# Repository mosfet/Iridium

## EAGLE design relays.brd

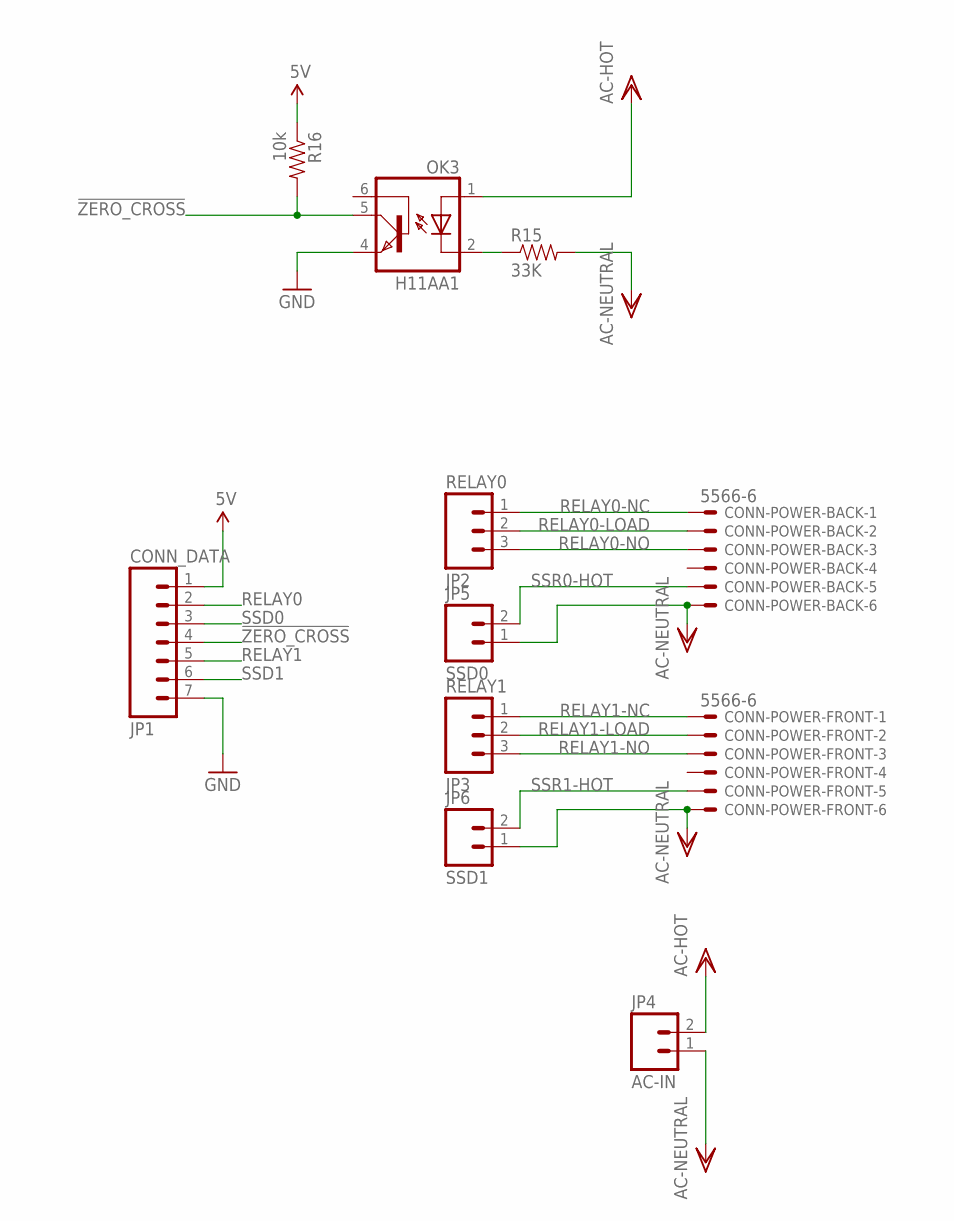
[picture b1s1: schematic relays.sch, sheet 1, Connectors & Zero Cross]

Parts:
CONN-POWER-BACK: 5566-6
CONN-POWER-FRONT: 5566-6
JP1: CONN_DATA; 1X07_LONGPADS
JP2: RELAY0; SCREWTERMINAL-5MM-3
JP3: RELAY1; SCREWTERMINAL-5MM-3
JP4: AC-IN; SCREWTERMINAL-5MM-2
JP5: SSD0; SCREWTERMINAL-5MM-2
JP6: SSD1; SCREWTERMINAL-5MM-2
OK3: H11AA1; DIL6-SMD
R15: 33K; 0603-RES
R16: 10k; 0603-RES

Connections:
5V: JP1.1, R16.1; also elsewhere on the board
!ZERO_CROSS: JP1.4, OK3.5 (COL), R16.2
AC-HOT: JP4.2, OK3.1 (A); also elsewhere on the board
AC-NEUTRAL: CONN-POWER-BACK.6, CONN-POWER-FRONT.6, JP4.1, JP5.1, JP6.1, R15.2
GND: JP1.7, OK3.4 (EMI); also elsewhere on the board
unnamed: OK3.2 (C), R15.1
RELAY0: JP1.2; also elsewhere on the board
RELAY0-LOAD: CONN-POWER-BACK.2, JP2.2; also elsewhere on the board
RELAY0-NC: CONN-POWER-BACK.1, JP2.1; also elsewhere on the board
RELAY0-NO: CONN-POWER-BACK.3, JP2.3; also elsewhere on the board
RELAY1: JP1.5; also elsewhere on the board
RELAY1-LOAD: CONN-POWER-FRONT.2, JP3.2; also elsewhere on the board
RELAY1-NC: CONN-POWER-FRONT.1, JP3.1; also elsewhere on the board
RELAY1-NO: CONN-POWER-FRONT.3, JP3.3; also elsewhere on the board
SSD0: JP1.3; also elsewhere on the board
SSD1: JP1.6; also elsewhere on the board
SSR0-HOT: CONN-POWER-BACK.5, JP5.2; also elsewhere on the board
SSR1-HOT: CONN-POWER-FRONT.5, JP6.2; also elsewhere on the board

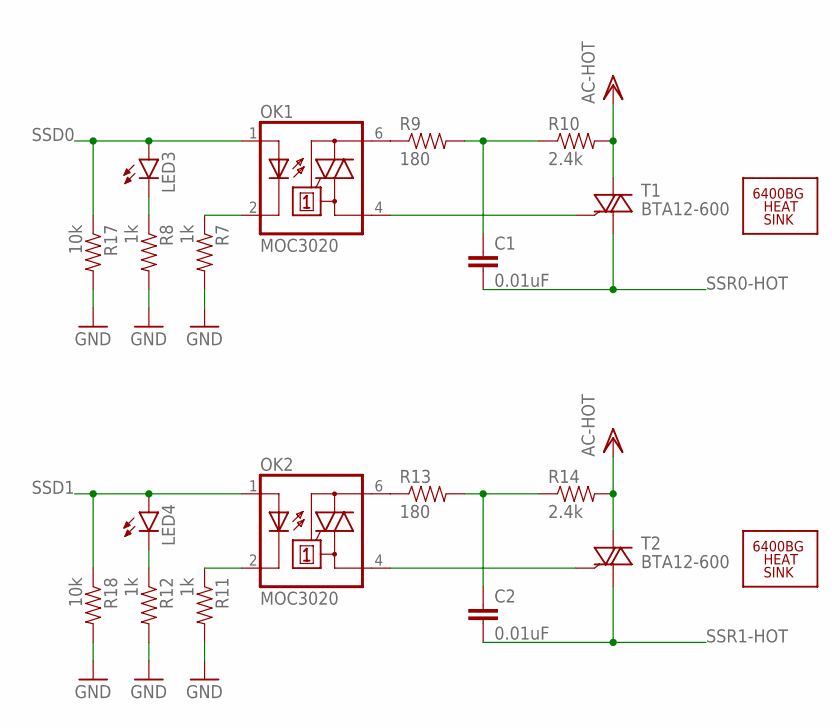
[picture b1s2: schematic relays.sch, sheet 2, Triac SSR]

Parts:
C1, C2: 0.01uF; 0603-CAP
LED3, LED4: LED0603; LED-0603
OK1, OK2: MOC3020; DIL6-SMD
R7, R8, R11, R12: 1k; 0603-RES
R9, R13: 180; 0603-RES
R10, R14: 2.4k; 0603-RES
R17, R18: 10k; 0603-RES
T1, T2: BTA12-600; TO220AB
U$3, U$4: 6400BG_HEATSINK

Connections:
AC-HOT: R10.2, R14.2, T1.2 (A2), T2.2 (A2); also elsewhere on the board
GND: R7.2, R8.2, R11.2, R12.2, R17.2, R18.2; also elsewhere on the board
unnamed: OK1.2 (C), R7.1
unnamed: LED3.C, R8.1
unnamed: OK1.6 (A2), R9.1
unnamed: C1.1, R9.2, R10.1
unnamed: OK2.2 (C), R11.1
unnamed: OK1.4 (A1), T1.3 (G)
unnamed: LED4.C, R12.1
unnamed: OK2.6 (A2), R13.1
unnamed: C2.1, R13.2, R14.1
unnamed: OK2.4 (A1), T2.3 (G)
SSD0: LED3.A, OK1.1 (A), R17.1; also elsewhere on the board
SSD1: LED4.A, OK2.1 (A), R18.1; also elsewhere on the board
SSR0-HOT: C1.2, T1.1 (A1); also elsewhere on the board
SSR1-HOT: C2.2, T2.1 (A1); also elsewhere on the board

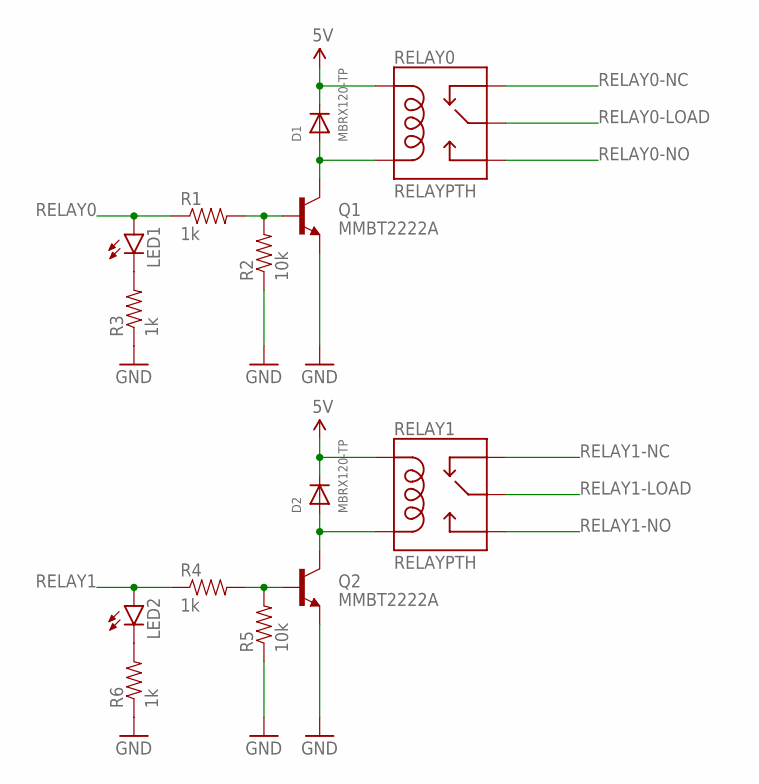
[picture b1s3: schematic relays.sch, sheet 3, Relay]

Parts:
D1, D2: MBRX120-TP; SOD-123
LED1, LED2: LED0603; LED-0603
Q1, Q2: MMBT2222A; SOT23-3
R1, R3, R4, R6: 1k; 0603-RES
R2, R5: 10k; 0603-RES
RELAY0, RELAY1: RELAYPTH; RELAY-G5Q

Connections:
5V: D1.C, D2.C, RELAY0.5 (COIL1), RELAY1.5 (COIL1); also elsewhere on the board
GND: Q1.2 (E), Q2.2 (E), R2.1, R3.1, R5.1, R6.1; also elsewhere on the board
unnamed: Q1.1 (B), R1.2, R2.2
unnamed: LED1.C, R3.2
unnamed: D1.A, Q1.3 (C), RELAY0.1 (COIL2)
unnamed: Q2.1 (B), R4.2, R5.2
unnamed: LED2.C, R6.2
unnamed: D2.A, Q2.3 (C), RELAY1.1 (COIL2)
RELAY0: LED1.A, R1.1; also elsewhere on the board
RELAY0-LOAD: RELAY0.2 (MAIN); also elsewhere on the board
RELAY0-NC: RELAY0.4 (NC); also elsewhere on the board
RELAY0-NO: RELAY0.3 (NO); also elsewhere on the board
RELAY1: LED2.A, R4.1; also elsewhere on the board
RELAY1-LOAD: RELAY1.2 (MAIN); also elsewhere on the board
RELAY1-NC: RELAY1.4 (NC); also elsewhere on the board
RELAY1-NO: RELAY1.3 (NO); also elsewhere on the board

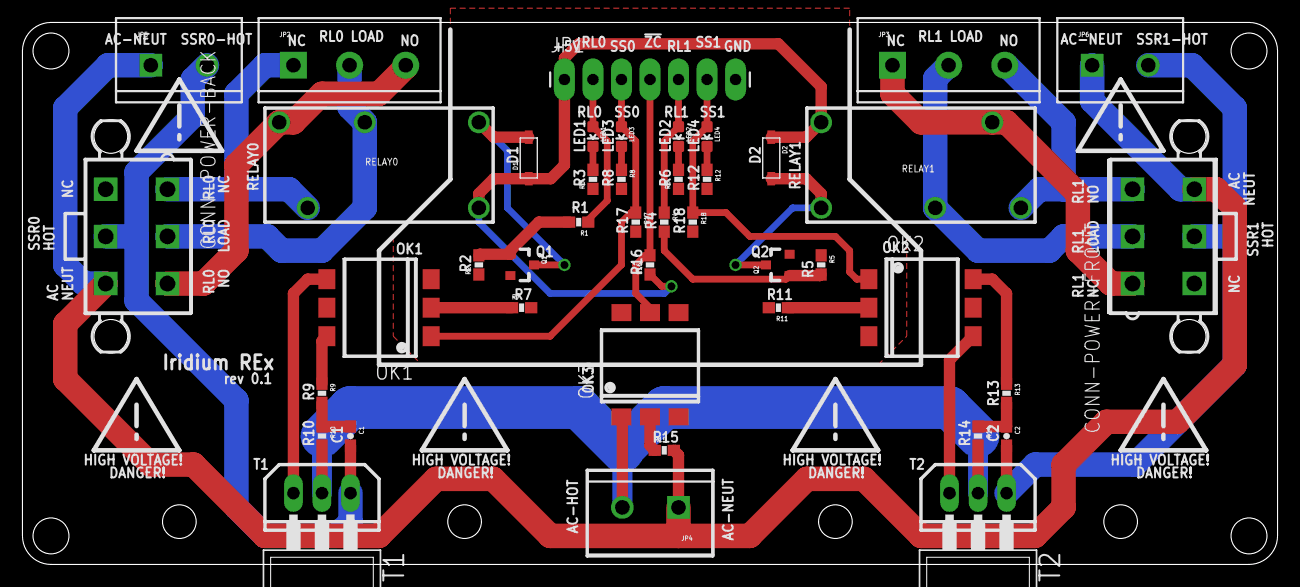
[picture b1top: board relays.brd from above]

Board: 2 copper layers, 111.8 x 48.3 mm, 45 parts (0 on the bottom side), 34 nets.

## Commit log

2015-06-16 :tada: Added .gitattributes & .gitignore files
2015-06-17 project checkin
2015-06-17 update ignore
2015-06-17 add some silkscreen
2015-06-17 update relay board, REx. Good boy.

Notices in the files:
parts and their libraries:
SparkFun-Electromechanical: Licensing: Creative Commons ShareAlike 4.0 International - https://creativecommons.org/licenses/by-sa/4.0
